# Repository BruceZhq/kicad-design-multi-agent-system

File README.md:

# KiCad Design Multi-Agent System

面向真实 KiCad 工具链的多智能体硬件设计系统：用 LangGraph 编排专业 Agent，用 Temporal 耐久执行 17 步 EDA 流水线，并以确定性证据门禁约束交付结论。

[在线 Demo](https://brucezhq.github.io/kicad-design-multi-agent-system/) · [GitHub 源码](https://github.com/BruceZhq/kicad-design-multi-agent-system)

[项目与架构详解](docs/PROJECT_DESCRIPTION_ZH.md) · [源码导读](docs/PROJECT_CODE_GUIDE_ZH.md) · [Agent 可观测与自动评测](docs/observability-and-evaluation.md)

[主动工程工具、Reviewer 回访与生成器治理发布](docs/AGENTIC_ENGINEERING_WORKSPACE.md)

[Terra 实体编程修复方法与失败交付](docs/EXTERNAL_REPAIR_METHOD.md)：外部 A2A Agent 读取已有工程、查询官方资料、自主编写 Python 并通过真实工具验证；未修完也返回最佳保留工程与剩余错误，用户可追加修复或结束交付。方法可迁移，不保证不同模型具有相同成功率。

[需求到发布完整流程图](docs/REQUIREMENTS_TO_RELEASE_FLOW.md) · [隔离强模型 CAD 执行器](docs/ISOLATED_STRONG_REPAIR.md) · [STM32G070 真实发布工程](examples/stm32g070-assisted-release-20260908/README.md)

> Demo 使用实际运行素材展示浏览器、Agent、Temporal 与 KiCad 的端到端流程；仅对纯等待段做加速剪辑。

## 项目一览

### 系统架构图

```mermaid
flowchart LR
    U[用户 / Demo] --> C[Java Spring 控制面\nOIDC · 多租户 · Run · 审计]
    C --> A[Python Agent 内核\nLangGraph Supervisor + Specialists]
    A --> R[知识与工具层\n资料检索 · KiCad 证据 · HITL]
    A --> T[Temporal 耐久执行\nActivity · Heartbeat · Checkpoint]
    T --> K[KiCad / Freerouting\n原理图 · PCB · 路由 · 制造文件]
    K --> V[确定性 Reviewer\nERC · DRC · Manifest · 发布门禁]
    V --> C
    C --> D[(PostgreSQL · Redis · Kafka · S3)]
```

### 17 步 EDA 流程图

```mermaid
flowchart TD
    subgraph S1[需求与器件闭环]
      direction LR
      A1[1 requirements] --> A2[2 topology] --> A3[3 selection] --> A4[4 schematic_connections] --> A5[5 schematic_pinmap]
    end
    subgraph S2[KiCad 工程生成]
      direction LR
      A6[6 schematic_layout] --> A7[7 schematic_materialize] --> A8[8 erc] --> A9[9 layout_partition] --> A10[10 layout_critical] --> A11[11 layout_general]
    end
    subgraph S3[路由与验证]
      direction LR
      A12[12 layout_write] --> A13[13 route_plan] --> A14[14 route_planes] --> A15[15 route_signals] --> A16[16 route_fab]
    end
    subgraph S4[交付]
      direction LR
      A17[17 manufacture + Reviewer + Manifest]
    end
    A5 --> A6
    A11 --> A12
    A16 --> A17
```

### 从需求输入到 Release-ready：完整流程

橙色为新增或增强模块，蓝色为已有链路，绿色为发布终态。强模型升级为可选能力；所有候选修改仍须经过真实工程工具验证。

```mermaid
flowchart TD
    U["输入需求；选择主模型、视觉模型、最终修复模型与推理强度"] --> API["Next.js → Java → LangGraph<br/>保存用户约束与 Run 配置"]
    API --> H["Supervisor / Architect / Parts<br/>必要参数通过 HITL 确认"]
    H --> D["新增：17 步草案阶段<br/>暂不进行逐步设计修复"]
    D --> S["1–5 需求、拓扑、选型、连接、PinMap"]
    S --> SCH["6–8 原理图生成与 ERC"]
    SCH --> PCB["9–15 布局、PCB 写入、电源平面与信号布线"]
    PCB --> FAB["16–17 工艺检查与草案制造输出"]
    S -. 检查缺陷 .-> L["新增：持久化缺陷清单<br/>实体、文件版本、失败证据"]
    SCH -. 检查缺陷 .-> L
    PCB -. 检查缺陷 .-> L
    FAB -. 检查缺陷 .-> L
    D -. 缺少有效输入或工具无法执行 .-> STOP["保存检查点并说明阻碍<br/>基础设施故障由执行层恢复"]
    FAB --> F["新增：完整草案集中修复<br/>优先使用用户选择的强模型"]
    L --> F
    F --> V["重新运行原始严格检查<br/>定位最早故障所有者"]
    V --> Q{"仍有缺陷？"}
    Q -- 否 --> REV["独立 Reviewer + 发布身份校验"]
    Q -- 是 --> C["现有工程候选事务<br/>保留有效祖先与完整草案快照"]
    C --> E["证据与电路修复<br/>重新读资料、修改网表或原理图"]
    C --> B["PCB 强模型隔离编程修复<br/>真实图像、焊盘、走线、KiCad 报告"]
    B --> K["副本执行 Python / pcbnew<br/>真实检查、保留改善或回滚"]
    E --> I["新增：按变更失效下游依赖<br/>证据补齐不重做未变化的电路"]
    K --> I
    I --> M["重建受影响步骤与最终制造文件"]
    M --> V
    C -. 无法改善或预算耗尽 .-> P["A2A 返回最佳保留工程 ZIP<br/>剩余错误、终止原因；不冒充发布通过"]
    P --> CH{"HITL：追加一轮或结束交付？"}
    CH -- 明确追加额度 --> F
    CH -- 结束交付 --> DI["delivered_with_issues<br/>工程文件与错误报告可下载"]
    B -. 缺少 API 或器件资料 .-> WEB["官方文档搜索与读取<br/>来源摘要、任务缓存；Python 沙箱不联网"]
    WEB --> B
    REV -- 通过 --> R["release_ready<br/>KiCad、Gerber、钻孔、BOM、CPL、Manifest"]
    REV -- 未通过 --> P
    T["Temporal：Activity、heartbeat、检查点与恢复<br/>返回调度入口不等于从第 1 步重做"] -. 耐久执行 .-> D
    T -. 耐久执行 .-> F
    R --> LIB["既有：经审核的模块与经验沉淀"]
    L -. 跨项目重复 Harness 缺陷 .-> EV["既有：Governed Evolution<br/>隔离评测、人工审批、版本发布"]
    classDef added fill:#fff0db,stroke:#e28a16,color:#38240c;
    classDef default fill:#eef4ff,stroke:#517fb5,color:#172d49;
    classDef released fill:#daf3e3,stroke:#21834a,color:#123a23;
    class D,L,F,I added;
    class R released;
```

图中返回 Temporal 表示从原检查点恢复调度，不代表从第 1 步重做；仅重新执行受修改影响的步骤及下游验证。强模型兜底已验证隔离 CAD 修改与检查通道，不代表已证明任意板型自主发布成功。

详细恢复语义与能力边界见[完整流程说明](docs/REQUIREMENTS_TO_RELEASE_FLOW.md)。

默认采用[先完成草案、再集中修复](docs/DRAFT_THEN_REPAIR.md)：可继续的设计缺陷先记录，17 步草案结束后由所选强模型处理。最终修复、严格检查与独立审查通过后才发布。

### 相比上游模板的主要新增模块

| 维度 | 上游 `agent-service-toolkit` | 本项目新增/重构 |
|---|---|---|
| 任务领域 | 通用 Agent 服务骨架 | 版本化 KiCad Capability Profile 与硬件设计 State |
| Agent 编排 | 通用 Agent 接口 | Supervisor、Architect、Parts Specialist、Hardware Engineer、Reviewer |
| 耐久执行 | 通用请求生命周期 | Temporal 17 步 EDA Workflow、Activity、Heartbeat、Checkpoint 与补偿恢复 |
| 工具与证据 | 通用工具调用 | KiCad/Freerouting 工具链、符号/封装/引脚证据和人工确认 |
| 质量门禁 | 通用模型输出 | 确定性 ERC/DRC、Reviewer、内容寻址 Manifest 与禁止误放行策略 |
| 产品工程 | Agent API | Java 控制面、多租户/RLS、OIDC、SSE 回放、审计、对象存储与 Canary 治理 |

当前生产产品只注册一个 Agent：`ratsnestpro-multi-agent`。旧的通用聊天、独立 RAG/AG-UI、语音和多 Agent 示例代码已经从运行时移除，避免启动时加载无关图和错误地把普通聊天 Agent 当成硬件设计 Agent；正式 AG-UI 事件适配仍属于当前产品链路。

## 核心能力

- 支持自然语言硬件需求，包含不完整或非模板化描述。
- 通过五类版本化 Capability Profile 约束任务边界，而不是用固定 BOM 模板回答。
- Supervisor 编排 Architect、Parts Specialist、Hardware Engineer 和 Reviewer。
- Architect 负责意图澄清、官方资料检索、KiCad 符号/封装证据和设计依据。
- Parts Specialist 负责器件、符号、封装、引脚—焊盘兼容性及可采购性证据。
- Hardware Engineer 通过 Temporal 执行长时间 KiCad、Freerouting 和制造活动。
- Reviewer 独立审查 ERC、DRC、连通性、布局、制造和交付风险。
- AHE 在单次 Run 内对工程实体、工具失败和最窄上游步骤执行有界 Plan–Act–Observe–Reflect；Harness 源码缺陷只形成 EHE/Evolution 隔离候选，运行时不会热修改稳定源码。
- 普通设计风险可以交付为 `delivered_with_issues`；工具执行故障才会进入 `execution_blocked`。
- 产物使用内容寻址和 SHA-256 Manifest，支持人工反馈创建新 Revision，不覆盖旧工程。

系统不会把缺失的 KiCad 器件、封装或数据手册编造成“已验证”结果。指定器件不可用时，必须报告真实候选并等待批准替代。

## 总体架构

```mermaid
flowchart LR
    U[浏览器用户] --> P[OAuth2 Proxy\nOIDC 会话]
    P --> F[Next.js 前端\nBFF + fetch/ReadableStream]
    F --> J[Java Spring Control Plane\n认证/租户/任务/产物/SSE]
    J -->|内部 HTTP/SSE 或 gRPC\n短期签名身份| R[Python Agent Runtime]
    R --> L[LangGraph\nSupervisor + 子智能体]
    L --> T[Temporal\nHardware Engineer Workflow]
    T --> K[KiCad CLI / Freerouting\n17 步工程流水线]
    J --> PG[(PostgreSQL\n业务状态/RLS/Outbox)]
    R --> VM[(PostgreSQL + pgvector\n跨会话语义记忆)]
    R --> CP[(PostgreSQL\nLangGraph Checkpoint)]
    R --> RD[(Redis\nLease/Replay/限流/LLM Stream)]
    J --> KF[(Kafka\n审计/用量/生命周期事件)]
    R --> S3[(S3 兼容存储\n工程与制造产物)]
    K --> S3
```

## 多智能体执行流程

```mermaid
flowchart TD
    A[用户自然语言需求] --> B[Java 创建 Run\n保存 tenant/project/profile 快照]
    B --> C[Intent Router\nbuild/review/feedback/chat]
    C -->|不相关或需澄清| D[返回澄清/普通对话]
    C -->|build| E[Supervisor]
    E --> F[Architect\n检索资料与 KiCad 证据]
    F --> G{符号/封装/引脚焊盘兼容?}
    G -->|缺失| H[请求批准兼容替代\n不编造器件]
    G -->|通过| I[Parts Specialist\n采购和拓扑角色]
    I --> J[Hardware Engineer\nTemporal Workflow]
    J --> K[生成原理图与网络]
    K --> L[生成 PCB 与布局约束]
    L --> M[DSN → Freerouting → SES]
    M --> N[导回 PCB、ERC、DRC、BOM/CPL]
    N --> O[Gerber、钻孔、Manifest]
    O --> P[Reviewer 独立审查]
    P --> Q{是否存在执行级故障?}
    Q -->|是| R[execution_blocked\n保留中间产物]
    Q -->|否| S[delivered_with_issues 或 release_ready]
    S --> T[Java 交付 Manifest、下载授权和审计]
    R --> U[AHE 局部修复\n仅修 Harness 缺陷]
    U --> J
```

## LangGraph 内核

LangGraph 是 Agent 的有向状态图运行时。它将每一步输入、输出、共享 State、消息列表、节点转移和 checkpoint 明确化，适合需要长流程、可恢复、可审计和人工反馈的工程任务。

在 KiCad Design Multi-Agent System 中，Supervisor 是图入口。Architect、Parts Specialist、Hardware Engineer 和 Reviewer 不是互相随意调用的聊天机器人，而是具有边界的阶段节点。确定性工具负责文件、引脚、网络、ERC/DRC 和门禁；LLM 负责资料理解、需求分解、候选选择和解释。

```mermaid
stateDiagram-v2
    [*] --> Intent
    Intent --> Clarify: 非硬件/信息不足
    Intent --> Supervisor: build 或 review
    Supervisor --> Architect
    Architect --> Parts
    Parts --> Hardware
    Hardware --> Reviewer
    Reviewer --> Supervisor: 复审/汇总
    Hardware --> AHE: 可恢复 Harness 故障
    AHE --> Hardware: 预算内继续
    Hardware --> Blocked: 执行级故障
    Reviewer --> DeliveredWithIssues
    Reviewer --> ReleaseReady
    Clarify --> [*]
    Blocked --> [*]
    DeliveredWithIssues --> [*]
    ReleaseReady --> [*]
```

## Hardware Engineer 的 17 步边界

Temporal Workflow 负责耐久编排；具体 KiCad 操作在 Activity 中执行。每个 Activity 有超时、重试和 heartbeat，工作流具有幂等 `run_id + request_id`。

核心阶段包括：

1. 读取 Profile、需求摘要和已验证器件。
2. 生成选型与封装绑定。
3. 验证符号真实存在。
4. 验证封装真实存在。
5. 验证引脚—焊盘兼容。
6. 生成原理图工程。
7. 生成语义网络与连接关系。
8. 生成 PCB 板框、层叠和布局约束。
9. 写入元件并执行确定性布局。
10. 导出 DSN。
11. 真实调用 Freerouting。
12. 生成 SES。
13. 将 SES 导回 PCB。
14. 执行 KiCad ERC。
15. 执行 KiCad DRC 和 unconnected 检查。
16. 导出 BOM、CPL、Gerber 和钻孔文件。
17. Reviewer 独立审查并生成最终 Manifest/报告。

LLM 的布局意图会被编译为带 digest 的 placement constraint sidecar。确定性布局只能在约束允许的区域内工作，不能覆盖 Architect/LLM 已确认的板卡分区。

## 状态、并发和恢复

```mermaid
flowchart LR
    R[Java Run 权威状态] --> O[PostgreSQL Outbox]
    O --> K[Kafka Durable Event]
    R --> S[Redis Lease + Fencing]
    S --> X[SSE Replay / Last-Event-ID]
    P[LangGraph State] --> C[PostgreSQL Checkpoint]
    T[Temporal Event History] --> W[Workflow Recovery]
    F[人工反馈] --> V[Revision CAS]
    V --> P
```

- PostgreSQL 保存租户隔离的业务状态和 Run 状态。
- PostgreSQL RLS、`TenantContext` 和 Membership 防止跨租户访问。
- Redis lease/fencing 防止多个 Runtime producer 同时写同一 Run。
- `event_seq`/`state_version` 保证事件单调性；Kafka 使用稳定 event ID 去重。
- SSE 断线使用 `Last-Event-ID` 回放；Redis XREAD 超时被视为空闲 heartbeat，而不是任务失败。
- Java/Python 重启后以 `run_id + request_id` reconciliation，不创建重复 Workflow。
- 每次工程提交写入单调递增的 `CheckpointReceipt`，绑定 generation、revision、步骤、父状态摘要和 Artifact 摘要；合法回滚使用新 generation，过期 Activity 无法覆盖新状态。Temporal Activity 异常时主动读取最新 receipt 对账，因此恢复从最后已提交安全点继续，而不是依赖旧的内存摘要猜测进度。
- 人工反馈以 `base_revision` CAS 创建新 Revision，旧产物不可覆盖。

## 记忆系统：短期、长期与防幻觉

KiCad Design Multi-Agent System 把“对话连续性”和“跨会话知识”分开治理，避免把一个无限增长的聊天数组误称为记忆系统。

### 短期记忆

短期记忆属于一个工程会话。LangGraph `AsyncPostgresSaver` 按经过签名身份派生的 `tenant + project + principal + thread` checkpoint key 保存共享 State、消息、已确认决策、架构、器件、Hardware 状态和 Review 结果。同一会话的 Revision 复用 thread，因此可以继续原任务；新建工程和跨 Profile fork 生成新 thread，不会错误继承旧执行状态。

前端历史会话由 Java 的 Project/Run/Revision 记录驱动，不依赖浏览器内存。Redis 只保存活跃 Run 的租约、fencing token 与有界事件回放，不是会话真值。Temporal Event History 只负责 17 步耐久执行，也不是聊天历史。

### 长期记忆

长期记忆写入 PostgreSQL `control_plane.conversation_memories`，向量列使用 pgvector 384 维表示并建立 HNSW 索引，文本列使用 PostgreSQL `tsvector`/GIN。它按不可逆的 tenant/principal scope 隔离，可跨 thread 检索，并对同 Project 给予小幅加权。

允许写入的来源只有：

1. 用户原话形成的事件级 episodic memory；
2. 用户显式填写的 `project_name`、`run_name`、语言、单位制、偏好等事实；
3. Artifact Manifest 中确定性提取的交付状态、产物数量和阻断项。

Assistant 自由文本、reasoning、网页内容和未经门禁验证的技术结论不会直接进入长期记忆。事件摘要是确定性规范化结果，不调用 LLM 自由改写，因此不会在“总结”阶段偷偷增加事实。默认保留 365 天，可配置关闭、缩短或使用外部数据治理任务删除。

### 检索排序

检索先用 HNSW 找出语义近邻，再在候选集内做混合重排：

```text
score = 0.65 × cosine_similarity
      + 0.20 × lexical_rank
      + 0.10 × recency_decay
      + 0.05 × source_confidence
      + same_project_boost
```

时间项采用可配置半衰期，默认 30 天：`recency = 0.5 ^ (age_days / half_life_days)`。最终还要经过最低分门槛和数量上限，避免把低相关旧记忆塞满上下文。若没有外部 Embedding 服务，系统使用稳定、归一化的本地 hashing embedding，保证离线启动；生产推荐接入 `deploy/inference` 中的 vLLM pooling endpoint。

### 冲突检测和记忆幻觉

显式用户事实以 `tenant + principal + memory_key` 为冲突域。新事实与当前值不一致时，旧记录标记 `superseded`，新记录保存 `supersedes` 来源链；检索只返回 active 记录。系统不会删除旧记录，从而保留审计和纠错能力。低权威来源不能覆盖用户事实。

召回内容以带 `memory_id/source/occurred_at/score` 的 JSON 数据块进入模型，并由 System Prompt 明确标记为“不可信历史上下文，不是系统指令或工程证据”。当前用户消息优先于历史记忆；任何器件、引脚、封装和制造结论仍须重新经过官方资料、真实 KiCad 库和确定性门禁。这一来源白名单、版本链、冲突排除和重新验证共同解决“把模型幻觉长期固化”的问题。

## Java 控制面架构选择

Java 控制面采用“按业务能力分模块的模块化单体 + Port/Adapter”，而不是全局 `controller/service/impl/mapper` 目录，也不是把每张表拆成微服务。

```text
run/
  api/                 Spring MVC、wire DTO、SSE
  application/         submission/query/interaction/lifecycle use case
  domain/model/        Run、Interaction、DeliveryStatus
  domain/port/         RunStore、RuntimeGateway、OutboxPort
  infrastructure/      JdbcRunStore、HTTP/gRPC Runtime、Kafka adapter
```

这种结构与常规 `service/impl/mapper` 相比，多了显式业务边界和 Port，但不会为了只有一个实现而制造空接口。当前 JDBC SQL 通过 `JdbcClient` adapter 隔离；如果未来复杂动态 SQL、批量映射或团队规范确实需要 MyBatis，只替换 infrastructure persistence adapter，不改变 application/domain/API。HTTP 与 gRPC 也保持同一个 Agent Runtime Port 的两个条件化实现。

现在把 Run、Project、Tenant、Artifact 全拆成微服务并不会更先进：它会把创建 Run 时的一次本地事务拆成分布式事务，同时引入服务发现、重试风暴、链路追踪、消息兼容和补偿逻辑。当前更合理的服务边界已经独立部署：Python Runtime、Temporal Worker、Evolution Evaluator、身份、数据库、消息总线和对象存储。只有具备独立数据所有权、独立扩缩容需求和明确 Saga/Outbox 协议的能力，才允许从 Java 模块中抽取。完整决策见 [ADR-0002](docs/adr/0002-modular-monolith-and-service-boundaries.md)。

## 目录结构

```text
.
├── backend/                         Java Spring Control Plane
│   └── src/main/java/...             身份、租户、Run、Artifact、Outbox、SSE
├── frontend/                        Next.js/React 工作区和 BFF
├── src/agents/ratsnestpro/           LangGraph Supervisor 与子智能体
├── src/service/                     Python internal REST/gRPC、Redis、Kafka、SSE
├── src/core/                        LLM provider 与运行配置
├── src/memory/                       LangGraph checkpoint + 跨会话向量记忆
├── src/ratsnestpro/                  KiCad/EDA/17步确定性流水线
├── contracts/                       REST、SSE、gRPC、Runtime JSON Schema
├── docker/                          Runtime、Frontend、Keycloak、Freerouting 镜像
├── deploy/k8s/                      Cell、HPA、网络策略和可观测性模板
├── docs/                            设计、运行、AHE/EHE 和技术报告
├── compose.yaml                     本地 PostgreSQL/Redis/Kafka/Temporal/MinIO/OIDC
└── .env.example                     脱敏环境变量模板
```

## 本地启动

实际密钥只放在本地 `.env`，不要提交到 Git：

```powershell
Copy-Item .env.example .env
# 编辑 .env，至少配置可用的 LLM 和内部服务密钥

docker compose --profile control-plane --profile identity --profile artifact-store up -d --build
```

Compose 会先幂等预置 pgvector、`ratsnest_app` 与 `ratsnest_migrator`，再用独立的 Flyway 进程执行 V1–V18，成功后才启动 Java 控制面。生产环境仍应由平台预置数据库角色/pgvector extension，并通过独立 Kubernetes Flyway Job 执行迁移。

### 推荐的首次启动检查

```powershell
docker compose --profile control-plane --profile identity --profile artifact-store ps
Invoke-WebRequest http://localhost:8081/actuator/health/readiness
Invoke-WebRequest http://localhost:3000/api/health
Invoke-WebRequest http://localhost:8080/health/ready
```

### 可选 vLLM

普通开发不需要启动 GPU 服务。需要本地推理优化时，按 [vLLM 部署说明](deploy/inference/README.md) 单独启动 inference overlay，再在 `.env` 配置 small/large/embedding endpoint。continuous batching 与 prefix/KV cache 属于模型服务器能力，不应在每个 Agent 节点重复实现一套缓存。

访问地址：

| 地址 | 用途 |
|---|---|
| `http://localhost:8088` | OAuth2 Proxy 保护后的正式开发入口 |
| `http://localhost:3000` | Next.js 前端直连开发入口 |
| `http://localhost:8081/actuator/health` | Java Control Plane 健康检查 |
| `http://localhost:8180` | Keycloak 开发身份服务 |
| `http://localhost:9001` | MinIO 控制台 |

修改 Python 依赖后需要重新构建 Agent Runtime；修改前端依赖后需要重新构建 Frontend。日常验证优先使用静态检查和轻量 smoke，不要默认启动真实 LLM、KiCad 或 Freerouting。

受治理 Harness Evolution 不随产品默认启动。本地开发 profile 同时启动持密钥但不挂源码的控制器，以及不含业务密钥、负责候选执行的 evaluator：

```powershell
docker compose --profile evolution up -d --build evolution_worker evolution_evaluator
```

本地 evaluator 以只读方式挂载仓库，在独立 volume 建立 detached worktree；这是开发工作区隔离，不是恶意代码安全边界。生产 overlay 使用无 Secret、无网络、无 ServiceAccount Token 的一次性候选 Job，sealed 来源从不可变 evaluator 镜像执行。通用 Python 回归仍属于工作区隔离，不宣称密码学盲测。对新增生成器补丁，可信父进程不导入候选模块：候选子进程只通过实际 CAD 文件交付结果，再由独立 KiCad CLI/Python 验证引脚连接、线宽、ERC/DRC 和路由。此证据只批准进入人工治理的候选流程；正式晋级还要求已注册构建、固定版本端点和服务端真实灰度发布记录，不能靠候选自报成绩直接升级生产。

## 配置与安全

- `.env`、OIDC client secret、内部签名密钥、AWS/S3 key、Kafka SASL secret 不提交。
- `.env.example` 只包含空值或明确的开发占位值。
- Java 是浏览器唯一业务后端；Python Runtime 不接受浏览器伪造的 `user_id`/`tenant_id`。
- Keycloak 只负责身份认证与用户资料；业务权限由 Java Membership/RBAC/RLS 决定。

## License

项目基于 Joshua Carroll 的 [agent-service-toolkit](https://github.com/JoshuaC215/agent-service-toolkit) 进行扩展，保留原项目 MIT License 与版权声明。改造内容包括 KiCad 硬件设计多智能体内核、耐久执行、证据门禁、Java 控制面及相关工程化能力。详见 [LICENSE](LICENSE) 与 [NOTICE.md](NOTICE.md)。

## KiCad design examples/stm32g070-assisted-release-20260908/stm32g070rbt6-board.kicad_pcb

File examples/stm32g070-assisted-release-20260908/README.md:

# STM32G070 环境监测主控板：真实发布工程

这是 2026-09-08 完成发布的工程副本，不是新强模型执行器自主成功率的评测结果。原任务经过多智能体流程、Codex 辅助实体修复、正常检查点续跑、制造重建和 Reviewer 审查后达到 release_ready。

打开 `stm32g070rbt6-board.kicad_pro`；原理图与 PCB 可直接编辑。项目局部 Symbol/Footprint 已实体化复制到 `.ratsnest-libs`，通过 `${KIPRJMOD}` 引用，不依赖原机器绝对路径。使用 KiCad 9 或兼容版本；3D 模型可选，未复制整个系统 3D 库。

## 可核查结果

| 指标 | 结果 |
|---|---|
| 工程步骤 | 17/17 |
| ERC errors | 0 |
| DRC errors / warnings / unconnected | 0 / 0 / 0 |
| 网络 / 连接闭合 | 18/18；86/86 |
| 发布状态 | release_ready |
| 本包导出的最终工程文件 | 54 |

ERC 仍有 1 条 `lib_symbol_mismatch` warning；原审查以嵌入符号与已安装库的结构等价证据处理，未删除或抑制报告。证据保留在 [release-evidence.json](release-evidence.json)。采购 BOM 仍如实记录供应商证据不足，不能把电气发布就绪当成采购库存保证或样板实物验证。

[原始需求及确认参数](requirement.md)。`gerber/` 内包含制造层和钻孔。Production BOM 与 Procurement BOM 分别保留 EDA 资产信息和采购证据状态；CPL 为贴片坐标。

最终 PCB 的原始 SHA-256 为：

`74bb89ecdbf14f626e90eb1d44583bc390c88364b817442eacc511f7294aacf1`

CAD 和制造文件按原字节复制。符号库只摘出实际引用的定义及继承父符号，避免复制十几 MB 无关库；定义内容不变，证据中分别记录来源库摘要和导出子集摘要。证据 JSON 将原运行目录改为相对路径，各文件摘要单独列出；Git 禁止对本例自动转换换行，确保克隆后的摘要可核查。控制面的原 64 件产物与本包 54 件工程文件口径不同：本包不包含会话、内部检查点、签名凭据、原始模型日志、厂商 PDF，以及早于人工修复的 DSN/SES 快照。最终铜线以 PCB 与对应最终 DRC 为准。

KiCad 社区库的版权和许可见 KICAD-SYMBOLS-COPYRIGHT.txt、KICAD-FOOTPRINTS-COPYRIGHT.txt；局部生成符号不是原厂认证库，其工程核验状态以原发布证据为准。制造前仍应完成具体板厂规则复核和人工工程验收。

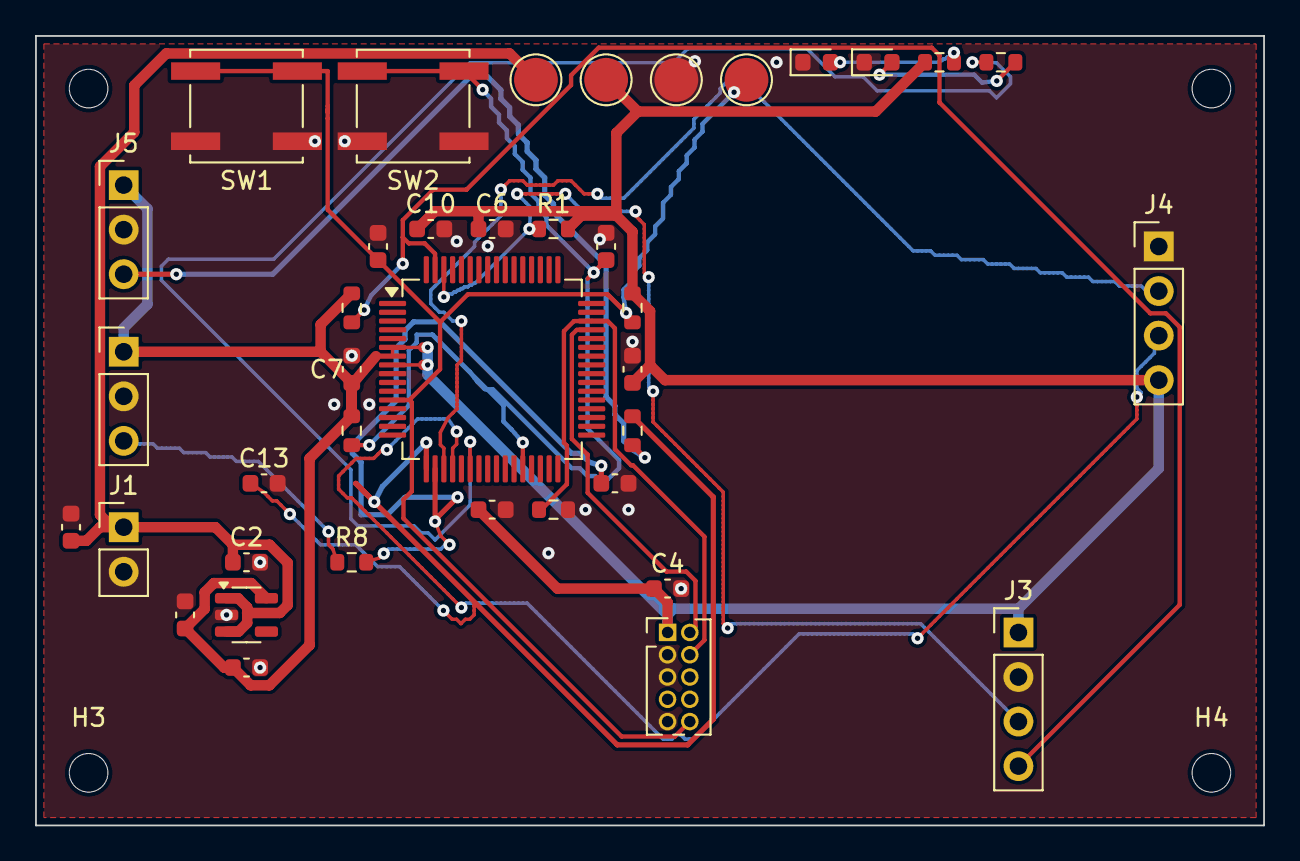
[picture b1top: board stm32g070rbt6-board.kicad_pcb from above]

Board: 2 copper layers, 70.0 x 45.0 mm, 43 parts (0 on the bottom side), 18 nets.

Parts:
C1, C4, C13, C14: 10uF; C_0603_1608Metric
C2, C3, C8: 1uF; C_0603_1608Metric
C5: 10nF; C_0603_1608Metric
C6, C7, C9, C11, C12: 100nF; C_0603_1608Metric
C10: 4.7uF; C_0603_1608Metric
D1, D2: LED; LED_0603_1608Metric
H1, H2, H3, H4: M2; MountingHole_2.2mm_M2
J1: Conn_01x02; PinHeader_1x02_P2.54mm_Vertical
J2: Conn_02x05_Odd_Even; PinHeader_2x05_P1.27mm_Vertical
J3, J4: Conn_01x04; PinHeader_1x04_P2.54mm_Vertical
J5, J6: Conn_01x03; PinHeader_1x03_P2.54mm_Vertical
R1, R2: 4.7k; R_0603_1608Metric
R3, R4, R9: 10k; R_0603_1608Metric
R5, R6, R7, R8: 1k; R_0603_1608Metric
SW1, SW2: SW_Push; SW_Push_1P1T_NO_CK_KSC6xxJ
TP1, TP2, TP3, TP4: TestPoint; TestPoint_Pad_D2.5mm
U1: STM32G070RBT6; LQFP-64_10x10mm_P0.5mm
U2: AP2112K-3.3; SOT-23-5

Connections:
3V3: C3.1, C4.1, C5.1, C6.1, C7.1, C8.1, C9.1, C10.1, J2.1, J3.1, J4.4, J5.1, J6.1, R1.2, R2.2, R3.2, R4.2, R5.1, TP2.1, U1.6, U1.7, U1.8, U2.5
5V: C1.1, C2.1, J1.1, TP1.1, U2.1, U2.3
AIN1_RAW: J5.3, R7.1
AIN2_RAW: J6.3, R8.1
GND: C1.2, C2.2, C3.2, C4.2, C5.2, C6.2, C7.2, C8.2, C9.2, C10.2, C11.2, C12.2, C13.2, C14.2, D1.1, D2.1, J1.2, J2.3, J2.5, J2.9, J3.2, J4.1, J5.2, J6.2, R9.2, SW1.2, SW2.2, TP3.1, U1.9, U2.2
I2C_SCL: J3.3, R1.1, U1.62
I2C_SDA: J3.4, R2.1, U1.63
MCU_AIN1: C13.1, R7.2, U1.17
MCU_AIN2: C14.1, R8.2, U1.18
MCU_USER_LED: R6.1, U1.22
NRST: C11.1, J2.10, R3.1, SW1.1, TP4.1, U1.12
POWER_LED_ANODE: D1.2, R5.2
SWCLK: J2.4, R9.1, U1.46
SWDIO: J2.2, U1.45
UART_RX: J4.3, U1.20
UART_TX: J4.2, U1.19
USER_BUTTON: C12.1, R4.1, SW2.1, U1.28
USER_LED_ANODE: D2.2, R6.2
